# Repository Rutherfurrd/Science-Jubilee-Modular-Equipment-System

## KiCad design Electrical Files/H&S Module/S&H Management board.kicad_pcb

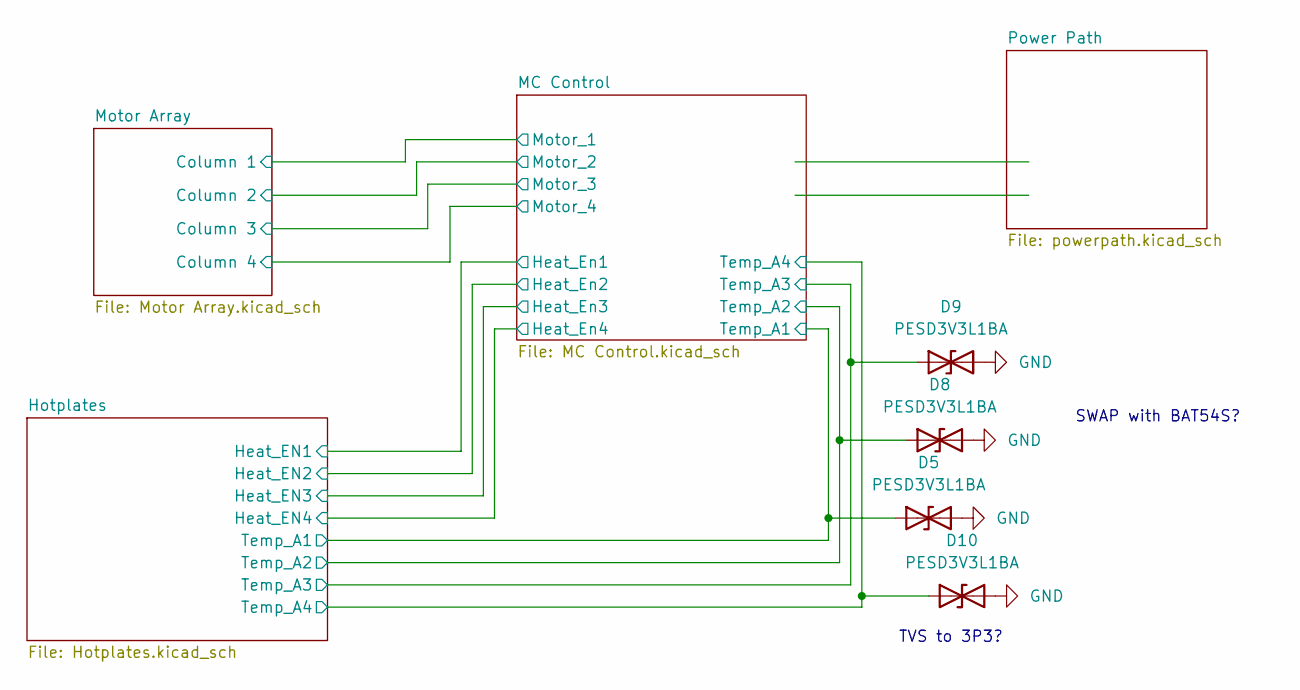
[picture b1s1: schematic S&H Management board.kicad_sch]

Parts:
D5, D8, D9, D10: PESD3V3L1BA; D_SOD-323F

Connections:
/Hotplates/Temp_A1: D5.1 (A1); also elsewhere on the board
/Hotplates/Temp_A2: D8.1 (A1); also elsewhere on the board
/Hotplates/Temp_A3: D9.1 (A1); also elsewhere on the board
/Hotplates/Temp_A4: D10.1 (A1); also elsewhere on the board
GND: D5.2 (A2), D8.2 (A2), D9.2 (A2), D10.2 (A2); also elsewhere on the board

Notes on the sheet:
SWAP with BAT54S?
TVS to 3P3?

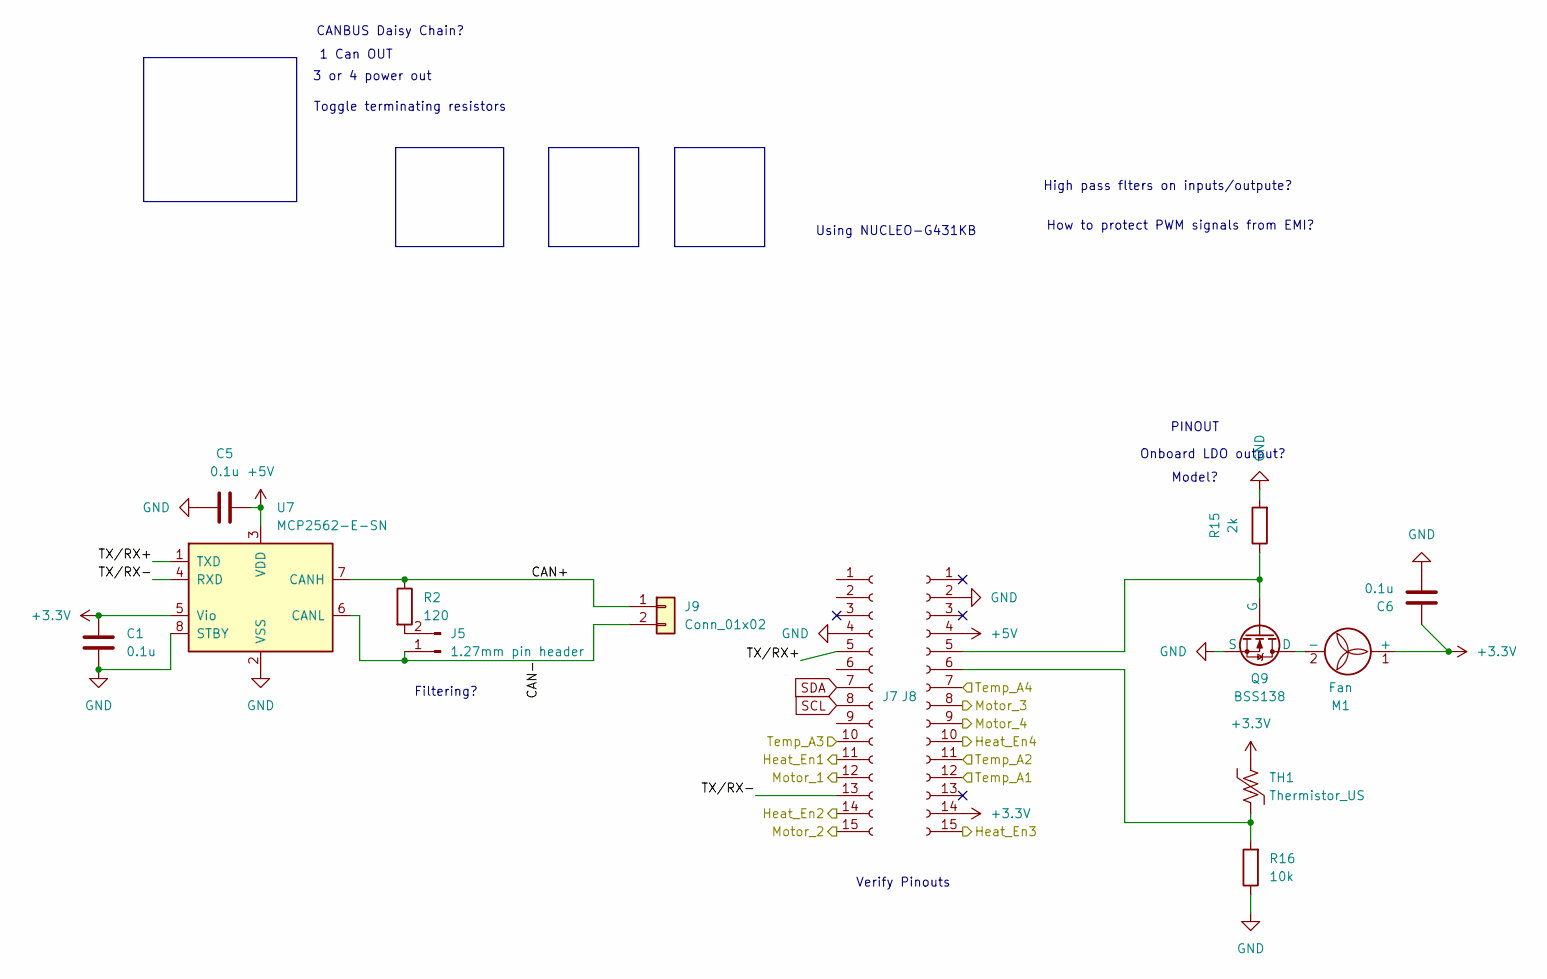
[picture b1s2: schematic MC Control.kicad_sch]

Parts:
C1, C5, C6: 0.1u; C_0603_1608Metric_Pad1.08x0.95mm_HandSolder
J5: 1.27mm pin header; PinHeader_1x02_P1.27mm_Vertical
J7, J8: PPTC151LFBN-RC; PinHeader_1x15_P2.54mm_Vertical
J9: Conn_01x02; Molex_Mini-Fit_Jr_5569-02A2_2x01_P4.20mm_Horizontal
M1: Fan; JST_PH_B2B-PH-K_1x02_P2.00mm_Vertical
Q9: BSS138; SOT-23-3
R2: 120; R_0603_1608Metric_Pad0.98x0.95mm_HandSolder
R15: 2k; R_0603_1608Metric_Pad0.98x0.95mm_HandSolder
R16: 10k; R_0603_1608Metric_Pad0.98x0.95mm_HandSolder
TH1: Thermistor_US; R_0603_1608Metric_Pad0.98x0.95mm_HandSolder
U7: MCP2562-E-SN; SOIC-8_3.9x4.9mm_P1.27mm; LCSC C124016

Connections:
+3.3V: C1.1, C6.1, J8.14, M1.1 (+), TH1.1, U7.5 (Vio); also elsewhere on the board
+5V: C5.2, J8.4, U7.3 (VDD); also elsewhere on the board
/Hotplates/Heat_EN1: J7.11; also elsewhere on the board
/Hotplates/Heat_EN2: J7.14; also elsewhere on the board
/Hotplates/Heat_EN3: J8.15; also elsewhere on the board
/Hotplates/Heat_EN4: J8.10; also elsewhere on the board
/Hotplates/Temp_A1: J8.12; also elsewhere on the board
/Hotplates/Temp_A2: J8.11; also elsewhere on the board
/Hotplates/Temp_A3: J7.10; also elsewhere on the board
/Hotplates/Temp_A4: J8.7; also elsewhere on the board
/MC Control/CAN+: J9.1, R2.1, U7.7 (CANH)
/MC Control/CAN-: J5.1, J9.2, U7.6 (CANL)
/MC Control/Motor_1: J7.12; also elsewhere on the board
/MC Control/Motor_2: J7.15; also elsewhere on the board
/MC Control/Motor_3: J8.8; also elsewhere on the board
/MC Control/Motor_4: J8.9; also elsewhere on the board
/MC Control/TX/RX+: J7.5, U7.1 (TXD)
/MC Control/TX/RX-: J7.13, U7.4 (RXD)
GND: C1.2, C5.1, C6.2, J7.4, J8.2, Q9.3 (S), R15.2, R16.1, U7.2 (VSS), U7.8 (STBY); also elsewhere on the board
unnamed: J5.2, R2.2
unnamed: J8.5, Q9.2 (G), R15.1
unnamed: J8.6, R16.2, TH1.2
unnamed: M1.2 (-), Q9.1 (D)
SCL: J7.8
SDA: J7.7

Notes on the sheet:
Using NUCLEO-G431KB
PINOUT
High pass flters on inputs/outpute?
Filtering?
3 or 4 power out
Onboard LDO output?
Verify Pinouts
CANBUS Daisy Chain?
Model?
How to protect PWM signals from EMI?
Toggle terminating resistors
1 Can OUT

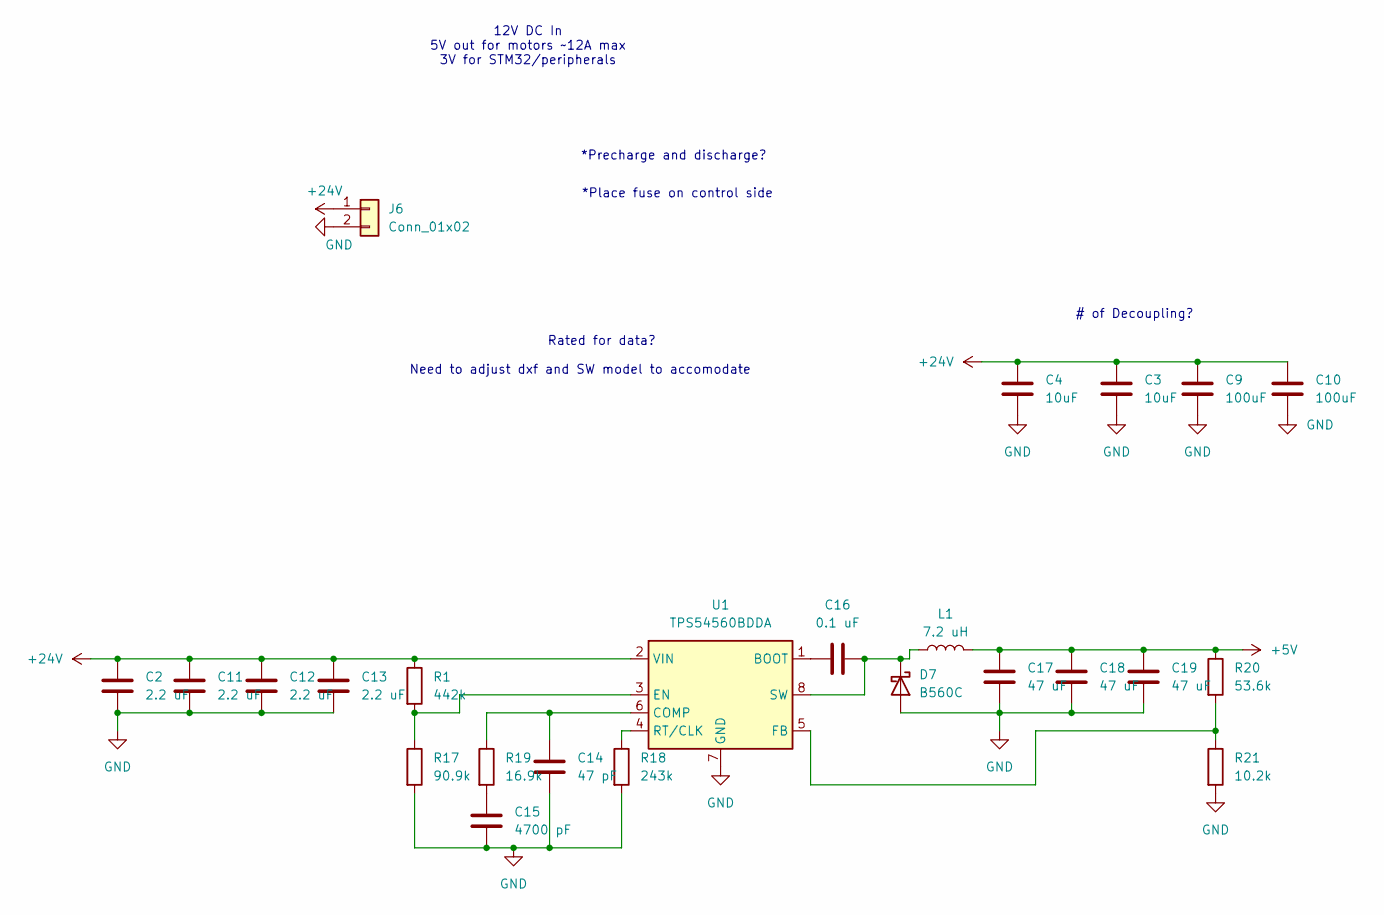
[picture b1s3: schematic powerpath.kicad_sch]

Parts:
C2, C11, C12, C13: 2.2 uF; C_0603_1608Metric_Pad1.08x0.95mm_HandSolder
C3, C4: 10uF; C_0603_1608Metric_Pad1.08x0.95mm_HandSolder
C9, C10: 100uF; C_0603_1608Metric_Pad1.08x0.95mm_HandSolder
C14: 47 pF; C_0603_1608Metric_Pad1.08x0.95mm_HandSolder
C15: 4700 pF; C_0603_1608Metric_Pad1.08x0.95mm_HandSolder
C16: 0.1 uF; C_0603_1608Metric_Pad1.08x0.95mm_HandSolder
C17, C18, C19: 47 uF; C_0603_1608Metric_Pad1.08x0.95mm_HandSolder
D7: B560C; D_SMC(DO-214AB)
J6: Conn_01x02; Molex_Mini-Fit_Jr_5569-02A2_2x01_P4.20mm_Horizontal
L1: 7.2 uH; L_Bourns_SRP7028A_7.3x6.6mm
R1: 442k; R_0603_1608Metric_Pad0.98x0.95mm_HandSolder
R17: 90.9k; R_0603_1608Metric_Pad0.98x0.95mm_HandSolder
R18: 243k; R_0603_1608Metric_Pad0.98x0.95mm_HandSolder
R19: 16.9k; R_0603_1608Metric_Pad0.98x0.95mm_HandSolder
R20: 53.6k; R_0603_1608Metric_Pad0.98x0.95mm_HandSolder
R21: 10.2k; R_0603_1608Metric_Pad0.98x0.95mm_HandSolder
U1: TPS54560BDDA; Texas_R-PDSO-G8_EP2.95x4.9mm_Mask2.4x3.1mm_ThermalVias

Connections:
+5V: C17.1, C18.1, C19.1, L1.2, R20.1; also elsewhere on the board
+24V: C2.1, C3.1, C4.1, C9.1, C10.1, C11.1, C12.1, C13.1, J6.1, R1.1, U1.2 (VIN); also elsewhere on the board
GND: C2.2, C3.2, C4.2, C9.2, C10.2, C11.2, C12.2, C13.2, C14.2, C15.2, C17.2, C18.2, C19.2, D7.2 (A), J6.2, R17.2, R18.2, R21.2, U1.7 (GND), U1.9 (GND); also elsewhere on the board
unnamed: C15.1, R19.2
unnamed: C16.2, D7.1 (K), L1.1, U1.8 (SW)
unnamed: C16.1, U1.1 (BOOT)
unnamed: C14.1, R19.1, U1.6 (COMP)
unnamed: R1.2, R17.1, U1.3 (EN)
unnamed: R20.2, R21.1, U1.5 (FB)
unnamed: R18.1, U1.4 (RT/CLK)

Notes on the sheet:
12V DC In 5V out for motors ~12A max 3V for STM32/peripherals
Need to adjust dxf and SW model to accomodate
Rated for data?
*Precharge and discharge?
# of Decoupling?
*Place fuse on control side

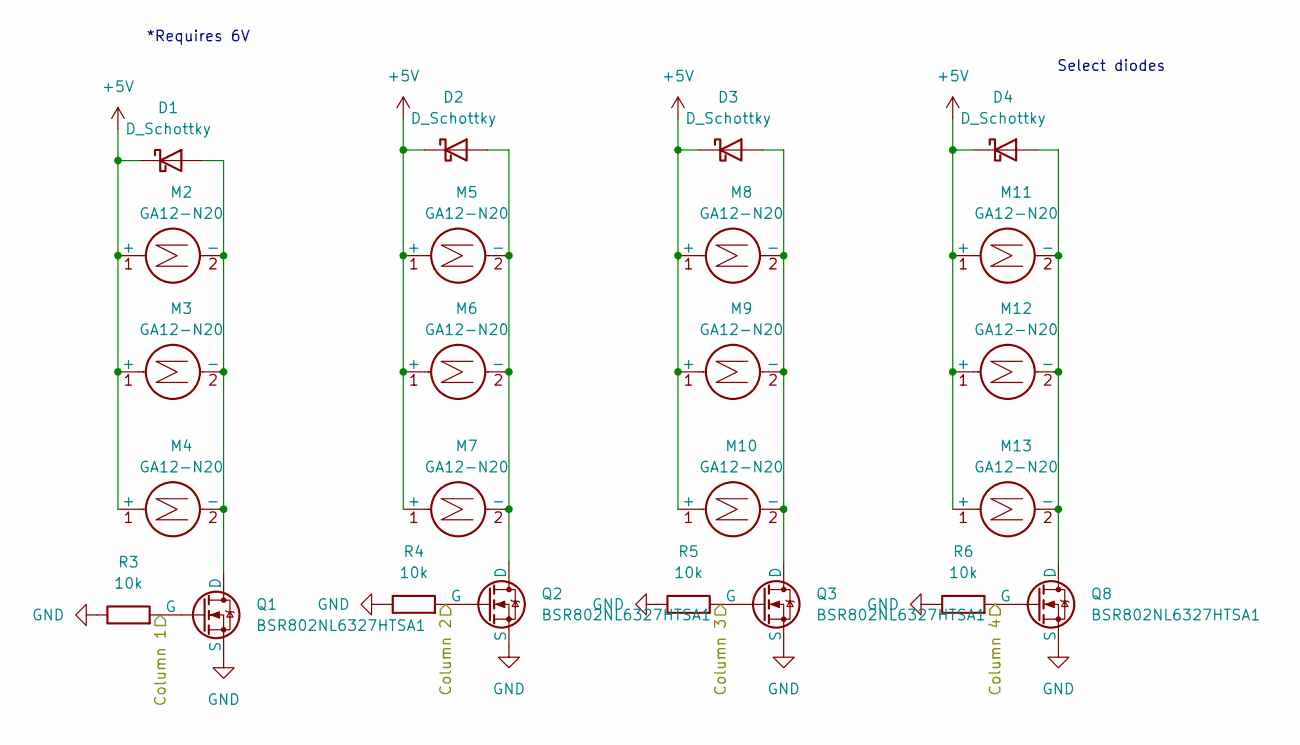
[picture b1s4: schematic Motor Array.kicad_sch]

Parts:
D1, D2, D3, D4: D_Schottky; D_SOD-323
M2, M3, M4, M5, M6, M7, M8, M9, M10, M11, M12, M13: GA12-N20
Q1, Q2, Q3, Q8: BSR802NL6327HTSA1; SC-59_Handsoldering
R3, R4, R5, R6: 10k; R_0603_1608Metric_Pad0.98x0.95mm_HandSolder

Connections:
+5V: D1.1 (K), D2.1 (K), D3.1 (K), D4.1 (K), M2.1 (+), M3.1 (+), M4.1 (+), M5.1 (+), M6.1 (+), M7.1 (+), M8.1 (+), M9.1 (+), M10.1 (+), M11.1 (+), M12.1 (+), M13.1 (+); also elsewhere on the board
/MC Control/Motor_1: Q1.2 (G), R3.2; also elsewhere on the board
/MC Control/Motor_2: Q2.2 (G), R4.2; also elsewhere on the board
/MC Control/Motor_3: Q3.2 (G), R5.2; also elsewhere on the board
/MC Control/Motor_4: Q8.2 (G), R6.2; also elsewhere on the board
GND: Q1.3 (S), Q2.3 (S), Q3.3 (S), Q8.3 (S), R3.1, R4.1, R5.1, R6.1; also elsewhere on the board
unnamed: D1.2 (A), M2.2 (-), M3.2 (-), M4.2 (-), Q1.1 (D)
unnamed: D2.2 (A), M5.2 (-), M6.2 (-), M7.2 (-), Q2.1 (D)
unnamed: D3.2 (A), M8.2 (-), M9.2 (-), M10.2 (-), Q3.1 (D)
unnamed: D4.2 (A), M11.2 (-), M12.2 (-), M13.2 (-), Q8.1 (D)

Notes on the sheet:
*Requires 6V
Select diodes

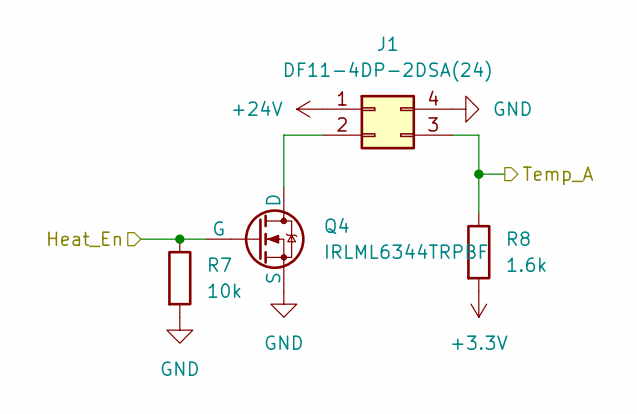
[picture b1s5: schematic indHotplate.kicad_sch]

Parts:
J1: DF11-4DP-2DSA(24); Hirose_DF11-4DP-2DSA_2x02_P2.00mm_Vertical
Q4: IRLML6344TRPBF; SC-59_Handsoldering
R7: 10k; R_0603_1608Metric_Pad0.98x0.95mm_HandSolder
R8: 1.6k; R_0603_1608Metric_Pad0.98x0.95mm_HandSolder

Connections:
+3.3V: R8.2; also elsewhere on the board
+24V: J1.1; also elsewhere on the board
/Hotplates/Heat_EN1: Q4.2 (G), R7.1; also elsewhere on the board
/Hotplates/Temp_A1: J1.3, R8.1; also elsewhere on the board
GND: J1.4, Q4.3 (S), R7.2; also elsewhere on the board
unnamed: J1.2, Q4.1 (D)

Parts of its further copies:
J2, J3, J4: DF11-4DP-2DSA(24); Hirose_DF11-4DP-2DSA_2x02_P2.00mm_Vertical
Q5, Q6, Q7: IRLML6344TRPBF; SC-59_Handsoldering
R9, R11, R13: 10k; R_0603_1608Metric_Pad0.98x0.95mm_HandSolder
R10, R12, R14: 1.6k; R_0603_1608Metric_Pad0.98x0.95mm_HandSolder

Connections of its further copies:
+3.3V: R10.2, R12.2, R14.2; also elsewhere on the board
+24V: J2.1, J3.1, J4.1; also elsewhere on the board
/Hotplates/Heat_EN2: Q5.2 (G), R9.1; also elsewhere on the board
/Hotplates/Heat_EN3: Q6.2 (G), R11.1; also elsewhere on the board
/Hotplates/Heat_EN4: Q7.2 (G), R13.1; also elsewhere on the board
/Hotplates/Temp_A2: J2.3, R10.1; also elsewhere on the board
/Hotplates/Temp_A3: J3.3, R12.1; also elsewhere on the board
/Hotplates/Temp_A4: J4.3, R14.1; also elsewhere on the board
GND: J2.4, J3.4, J4.4, Q5.3 (S), Q6.3 (S), Q7.3 (S), R9.2, R11.2, R13.2; also elsewhere on the board
unnamed: J2.2, Q5.1 (D)
unnamed: J3.2, Q6.1 (D)
unnamed: J4.2, Q7.1 (D)

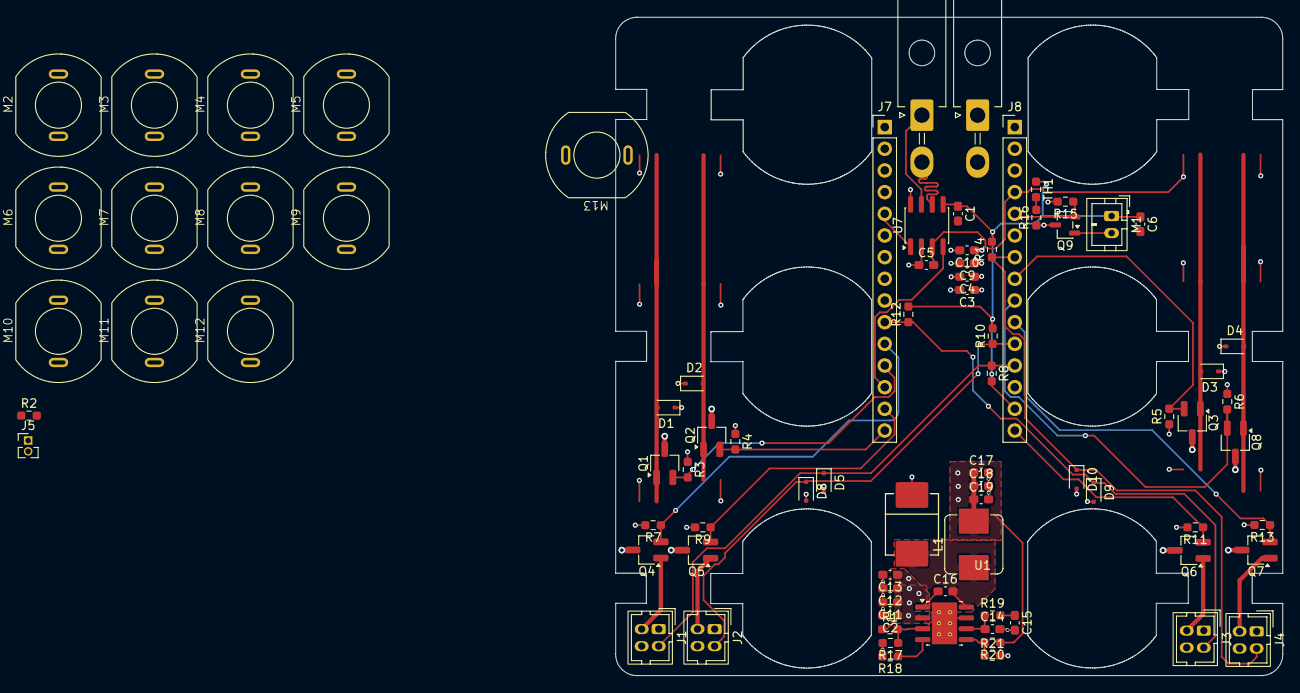
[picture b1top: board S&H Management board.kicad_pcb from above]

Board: 4 copper layers, 78.2 x 77.2 mm, 82 parts (0 on the bottom side), 39 nets.

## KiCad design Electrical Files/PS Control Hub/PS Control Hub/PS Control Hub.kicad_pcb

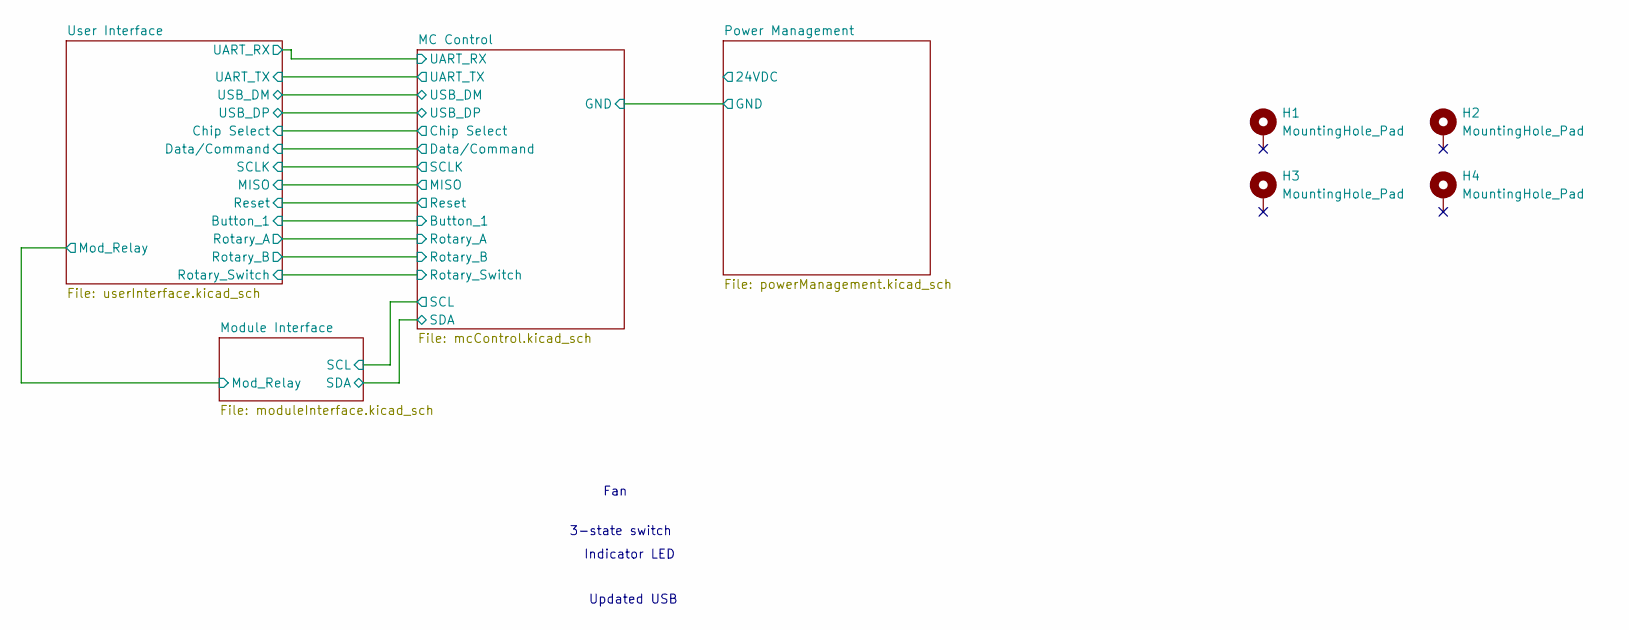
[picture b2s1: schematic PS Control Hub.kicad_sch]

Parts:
H1, H2, H3, H4: MountingHole_Pad; MountingHole_3.2mm_M3_DIN965_Pad_TopBottom

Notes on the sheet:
Updated USB
Fan
Indicator LED
3-state switch

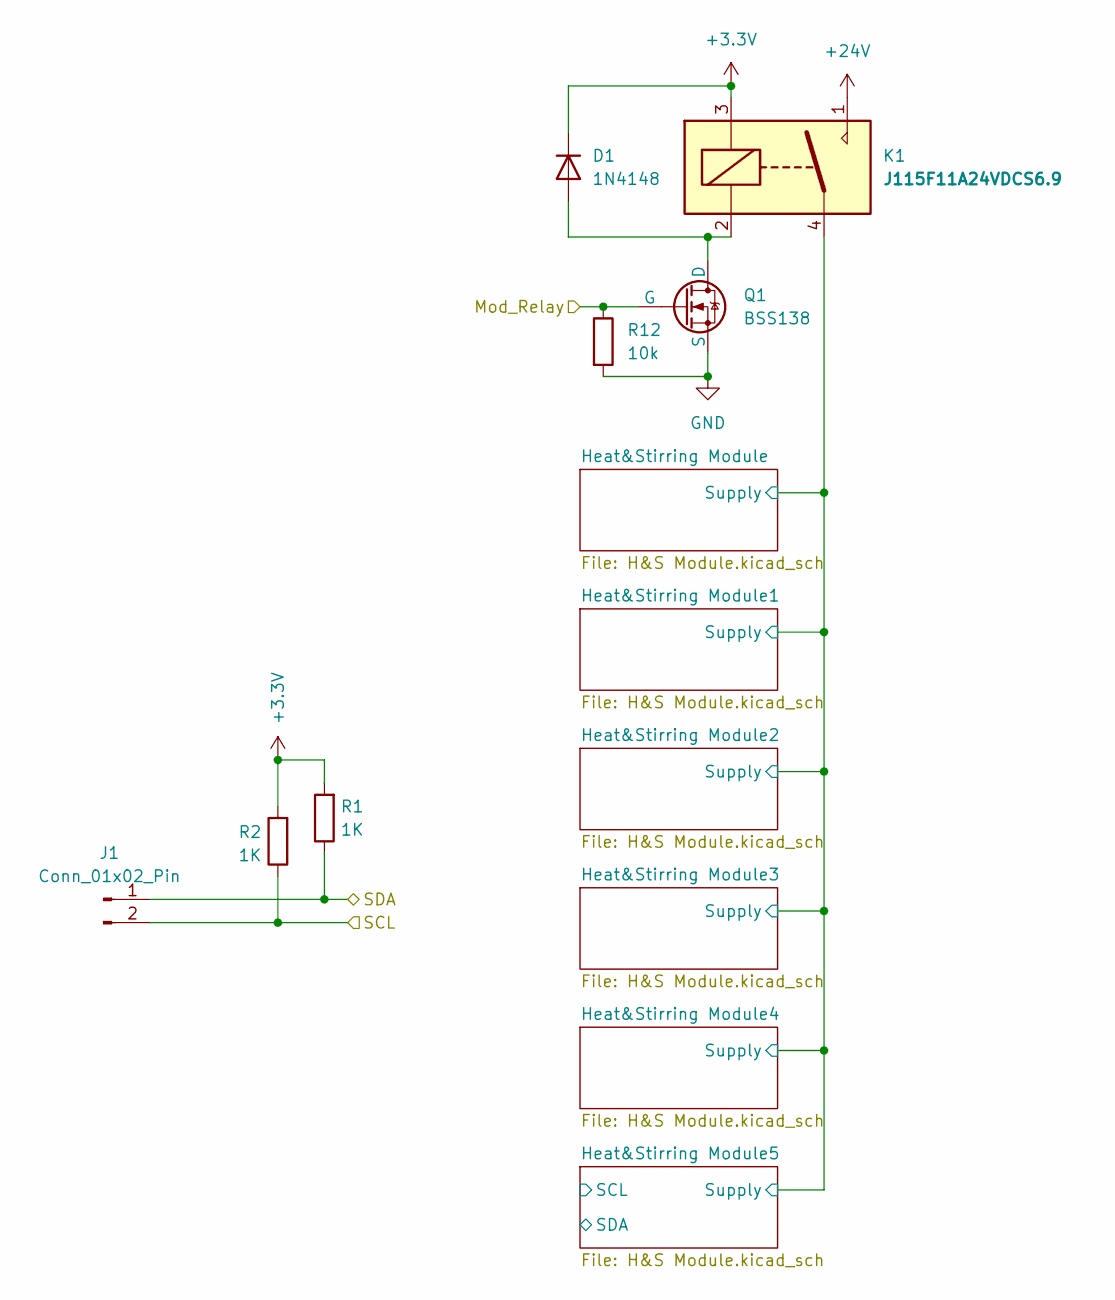
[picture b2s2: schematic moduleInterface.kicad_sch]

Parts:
D1: 1N4148; D_DO-35_SOD27_P7.62mm_Horizontal
J1: Conn_01x02_Pin; Molex_Mini-Fit_Jr_5566-02A_2x01_P4.20mm_Vertical
K1: J115F11A24VDCS6.9; J115F1_1A_S_6_CRS
Q1: BSS138; SOT-23-3
R1, R2: 1K; R_0805_2012Metric_Pad1.20x1.40mm_HandSolder
R12: 10k; R_0805_2012Metric_Pad1.20x1.40mm_HandSolder

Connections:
+3.3V: D1.1 (K), K1.3, R1.2, R2.2; also elsewhere on the board
+24V: K1.1; also elsewhere on the board
/MC Control/SCL: J1.2, R2.1; also elsewhere on the board
/MC Control/SDA: J1.1, R1.1; also elsewhere on the board
/Module Interface/Heat&Stirring Module/Supply: K1.4; also elsewhere on the board
/Module Interface/Mod_Relay: Q1.2 (G), R12.1; also elsewhere on the board
GND: Q1.3 (S), R12.2; also elsewhere on the board
unnamed: D1.2 (A), K1.2, Q1.1 (D)

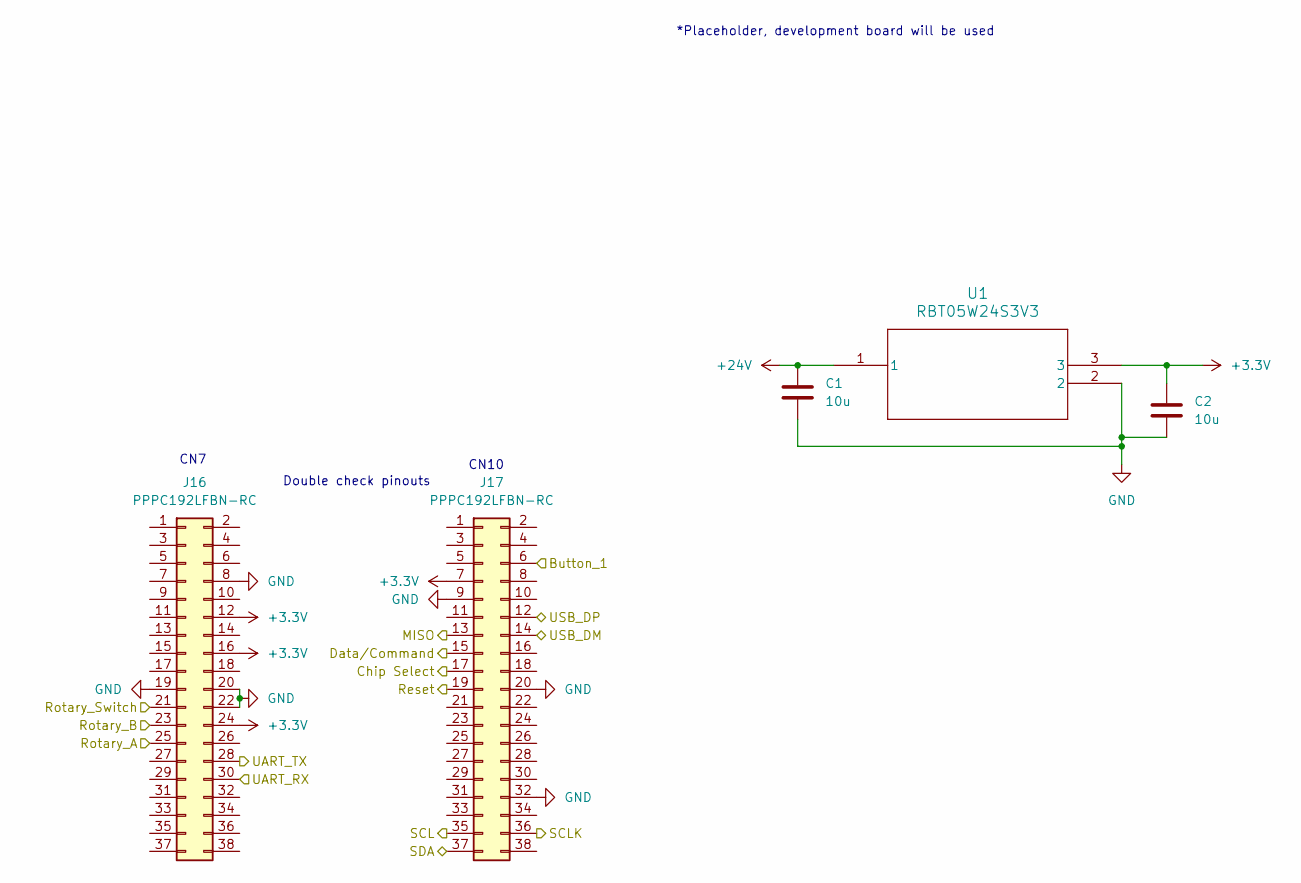
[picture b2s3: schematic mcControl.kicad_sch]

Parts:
C1, C2: 10u; C_0805_2012Metric_Pad1.18x1.45mm_HandSolder
J16, J17: PPPC192LFBN-RC; PinSocket_2x19_P2.54mm_Vertical
U1: RBT05W24S3V3; RBT10W24S05_XPP_XPR

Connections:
+3.3V: C2.1, J16.12, J16.16, J16.24, J17.7, U1.3; also elsewhere on the board
+24V: C1.1, U1.1; also elsewhere on the board
/MC Control/Button_1: J17.6; also elsewhere on the board
/MC Control/Chip Select: J17.17; also elsewhere on the board
/MC Control/Data/Command: J17.15; also elsewhere on the board
/MC Control/MISO: J17.13; also elsewhere on the board
/MC Control/Reset: J17.19; also elsewhere on the board
/MC Control/Rotary_A: J16.25; also elsewhere on the board
/MC Control/Rotary_B: J16.23; also elsewhere on the board
/MC Control/Rotary_Switch: J16.21; also elsewhere on the board
/MC Control/SCL: J17.35; also elsewhere on the board
/MC Control/SCLK: J17.36; also elsewhere on the board
/MC Control/SDA: J17.37; also elsewhere on the board
/MC Control/UART_RX: J16.30; also elsewhere on the board
/MC Control/UART_TX: J16.28; also elsewhere on the board
/MC Control/USB_DM: J17.14
/MC Control/USB_DP: J17.12
GND: C1.2, C2.2, J16.8, J16.19, J16.20, J16.22, J17.9, J17.20, J17.32, U1.2; also elsewhere on the board

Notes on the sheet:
Double check pinouts
*Placeholder, development board will be used
CN10
CN7

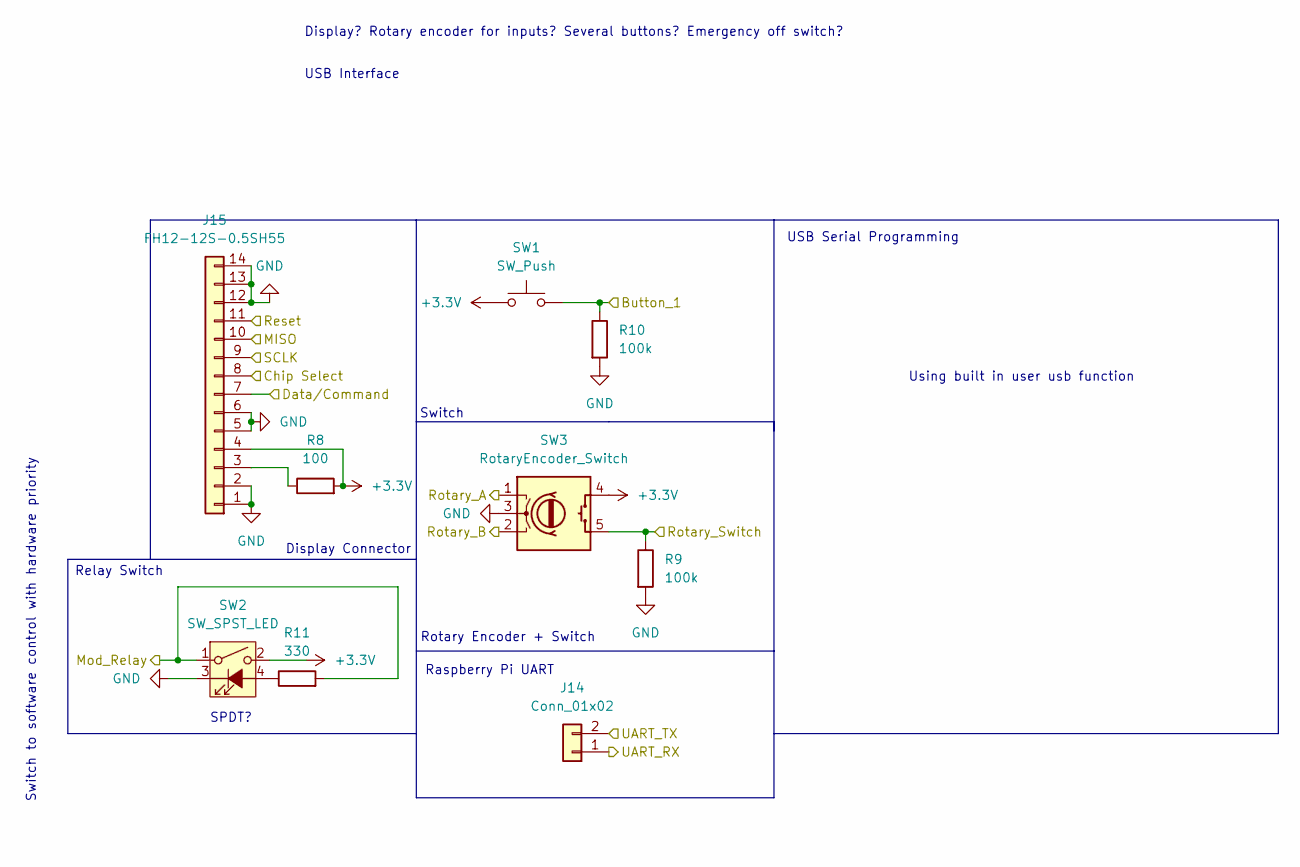
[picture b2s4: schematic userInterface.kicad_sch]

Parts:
J14: Conn_01x02; Molex_Mini-Fit_Jr_5566-02A_2x01_P4.20mm_Vertical
J15: FH12-12S-0.5SH55
R8: 100; R_0805_2012Metric_Pad1.20x1.40mm_HandSolder
R9, R10: 100k; R_0805_2012Metric_Pad1.20x1.40mm_HandSolder
R11: 330; R_0805_2012Metric_Pad1.20x1.40mm_HandSolder
SW1: SW_Push; JST_PH_B2B-PH-K_1x02_P2.00mm_Vertical
SW2: SW_SPST_LED; JST_PH_B4B-PH-K_1x04_P2.00mm_Vertical
SW3: RotaryEncoder_Switch; JST_PH_B5B-PH-K_1x05_P2.00mm_Vertical

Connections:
+3.3V: J15.4, R8.2, SW1.1, SW2.2, SW3.4 (S1); also elsewhere on the board
/MC Control/Button_1: R10.1, SW1.2; also elsewhere on the board
/MC Control/Chip Select: J15.8; also elsewhere on the board
/MC Control/Data/Command: J15.7; also elsewhere on the board
/MC Control/MISO: J15.10; also elsewhere on the board
/MC Control/Reset: J15.11; also elsewhere on the board
/MC Control/Rotary_A: SW3.1 (A); also elsewhere on the board
/MC Control/Rotary_B: SW3.2 (B); also elsewhere on the board
/MC Control/Rotary_Switch: R9.1, SW3.5 (S2); also elsewhere on the board
/MC Control/SCLK: J15.9; also elsewhere on the board
/MC Control/UART_RX: J14.1; also elsewhere on the board
/MC Control/UART_TX: J14.2; also elsewhere on the board
/Module Interface/Mod_Relay: R11.2, SW2.1; also elsewhere on the board
GND: J15.1, J15.2, J15.5, J15.6, J15.12, J15.13, J15.14, R9.2, R10.2, SW2.3 (K), SW3.3 (C); also elsewhere on the board
unnamed: J15.3, R8.1
unnamed: R11.1, SW2.4 (A)

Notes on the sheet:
Switch
USB Serial Programming
Display? Rotary encoder for inputs? Several buttons? Emergency off switch?
Relay Switch
Raspberry Pi UART
USB Interface
Display Connector
Rotary Encoder + Switch
Switch to software control with hardware priority
Using built in user usb function
SPDT?

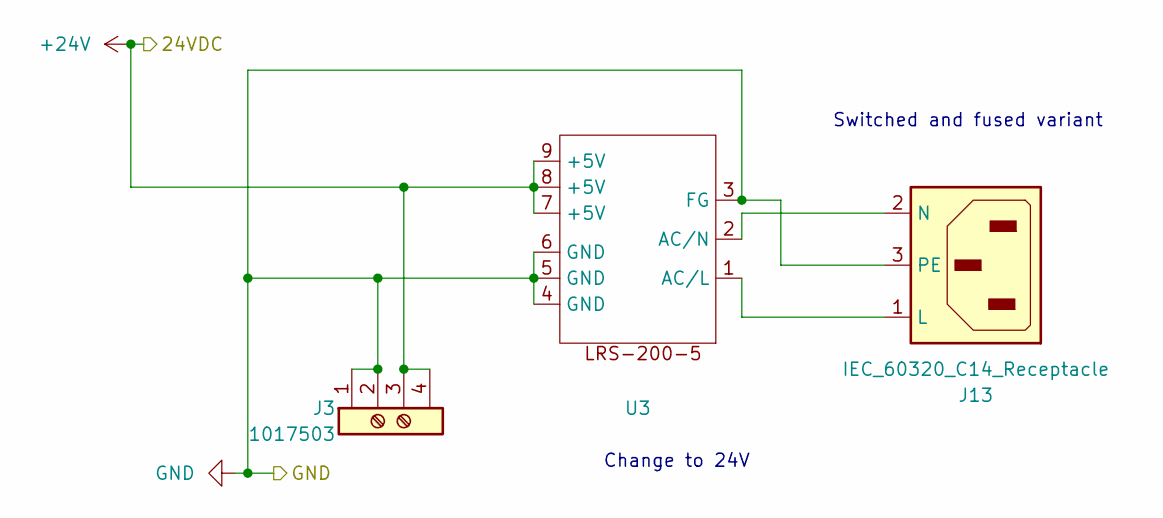
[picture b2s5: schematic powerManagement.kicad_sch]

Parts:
J3: 1017503; CONN_1017491
J13: IEC_60320_C14_Receptacle
U3: (no value)

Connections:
+24V: J3.3 (Pin_2), J3.4 (Pin_2), U3.7 (+5V), U3.8 (+5V), U3.9 (+5V); also elsewhere on the board
GND: J3.1, J3.2 (Pin_1), J13.3 (PE), U3.3 (FG), U3.4 (GND), U3.5 (GND), U3.6 (GND); also elsewhere on the board
unnamed: J13.1 (L), U3.1 (AC/L)
unnamed: J13.2 (N), U3.2 (AC/N)

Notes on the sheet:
Switched and fused variant
Change to 24V

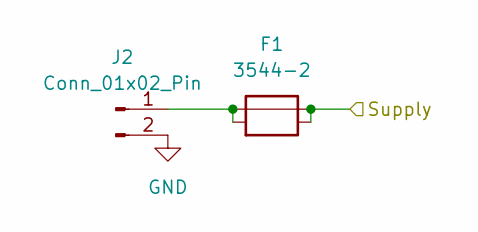
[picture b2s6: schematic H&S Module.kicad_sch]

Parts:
F1: 3544-2; CONN_3544-2_KEY
J2: Conn_01x02_Pin; Molex_Mini-Fit_Jr_5566-02A_2x01_P4.20mm_Vertical

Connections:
/Module Interface/Heat&Stirring Module/Supply: F1.3, F1.4; also elsewhere on the board
GND: J2.2; also elsewhere on the board
unnamed: F1.1, F1.2, J2.1

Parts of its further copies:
F2, F3, F4, F5, F6: 3544-2; CONN_3544-2_KEY
J4, J6, J8, J10, J12: Conn_01x02_Pin; Molex_Mini-Fit_Jr_5566-02A_2x01_P4.20mm_Vertical

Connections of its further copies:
/Module Interface/Heat&Stirring Module/Supply: F2.3, F2.4, F3.3, F3.4, F4.3, F4.4, F5.3, F5.4, F6.3, F6.4; also elsewhere on the board
GND: J4.2, J6.2, J8.2, J10.2, J12.2; also elsewhere on the board
unnamed: F2.1, F2.2, J4.1
unnamed: F3.1, F3.2, J6.1
unnamed: F4.1, F4.2, J8.1
unnamed: F5.1, F5.2, J10.1
unnamed: F6.1, F6.2, J12.1

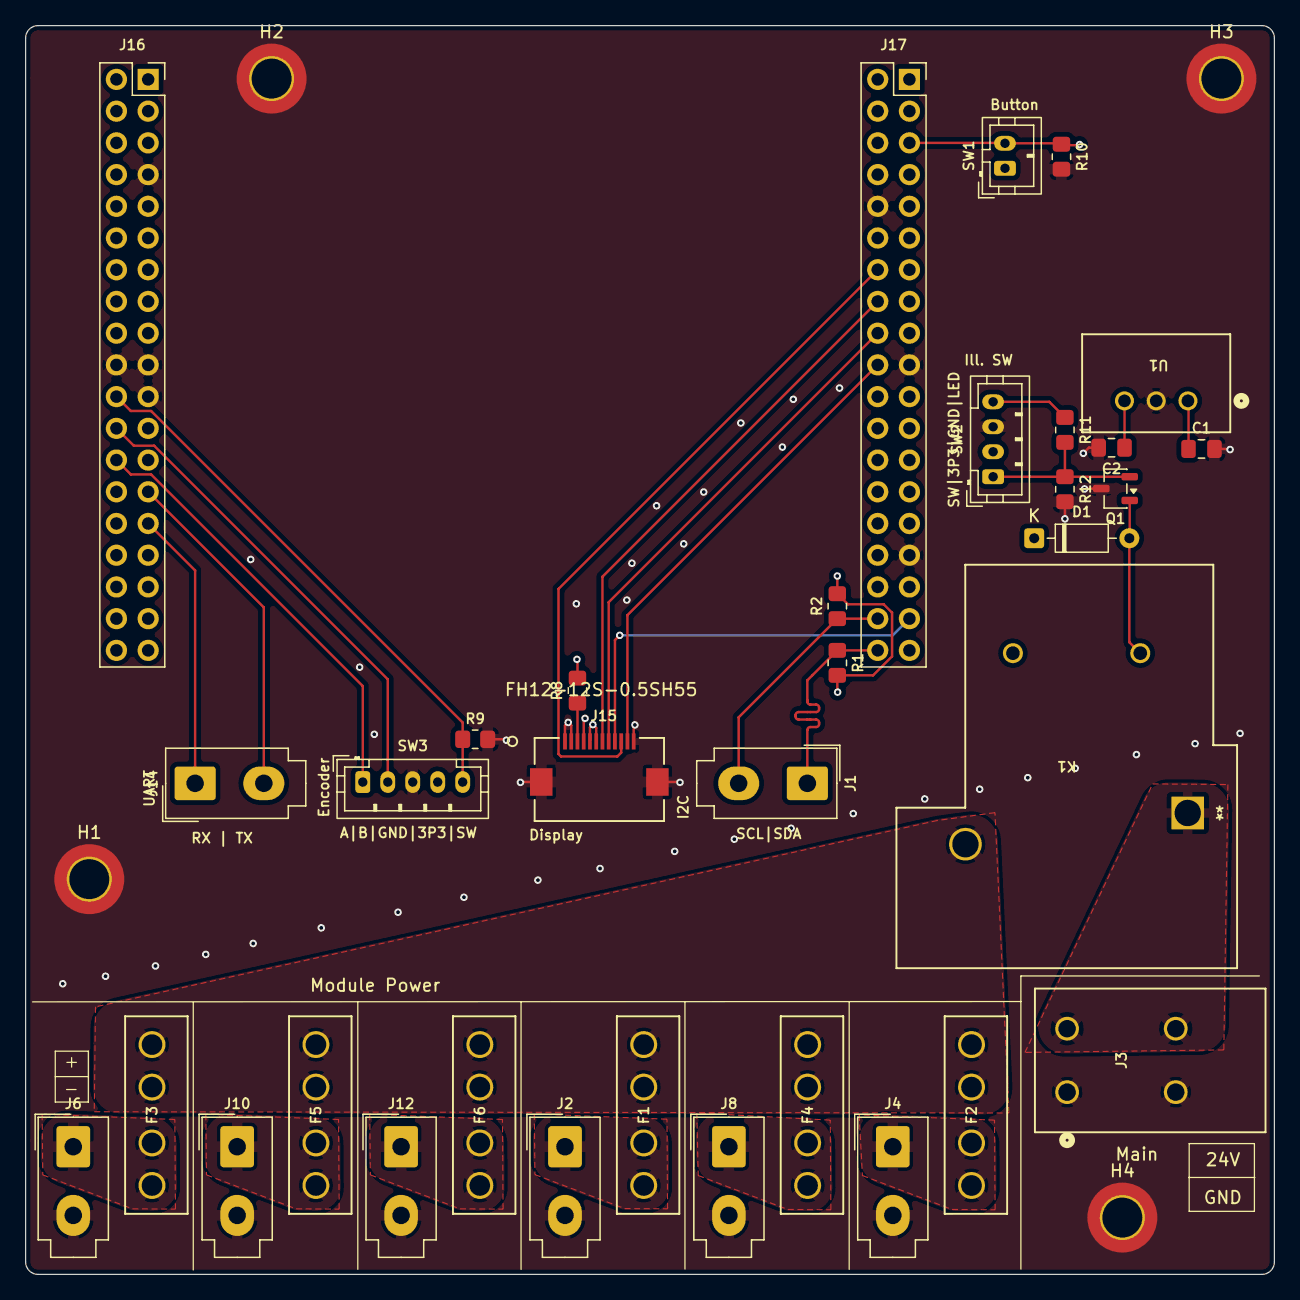
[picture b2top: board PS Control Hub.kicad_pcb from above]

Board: 4 copper layers, 100.0 x 100.0 mm, 38 parts (0 on the bottom side), 27 nets.

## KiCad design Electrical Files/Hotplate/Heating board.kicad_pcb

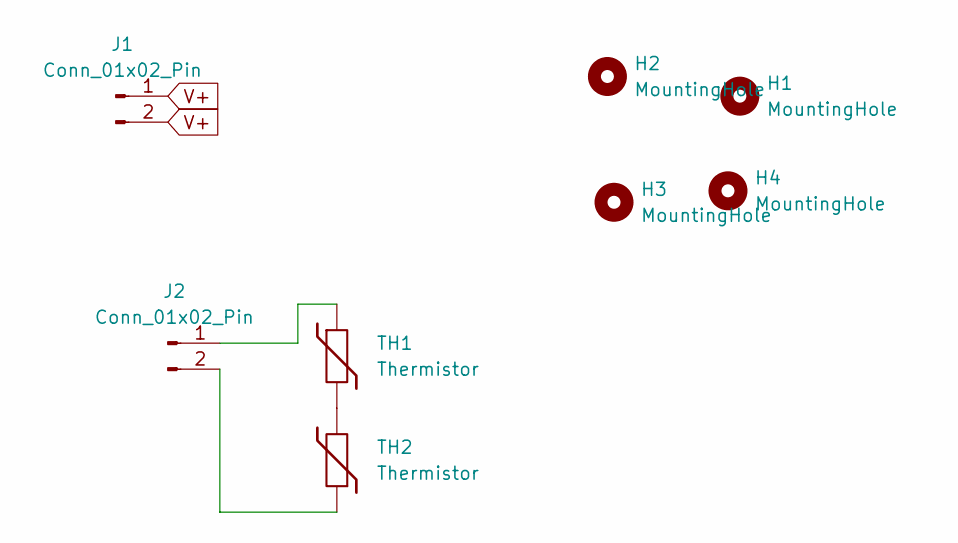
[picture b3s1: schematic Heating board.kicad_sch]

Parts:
H1, H2, H3, H4: MountingHole; MountingHole_2.2mm_M2_DIN965_Pad_TopBottom
J1, J2: Conn_01x02_Pin; SolderWire-0.1sqmm_1x02_P3.6mm_D0.4mm_OD1mm
TH1: Thermistor; C_0603_1608Metric_Pad1.08x0.95mm_HandSolder
TH2: Thermistor; R_0603_1608Metric_Pad0.98x0.95mm_HandSolder

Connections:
unnamed: J2.1, TH1.1
unnamed: J2.2, TH2.1
unnamed: TH1.2, TH2.2
V+: J1.1, J1.2

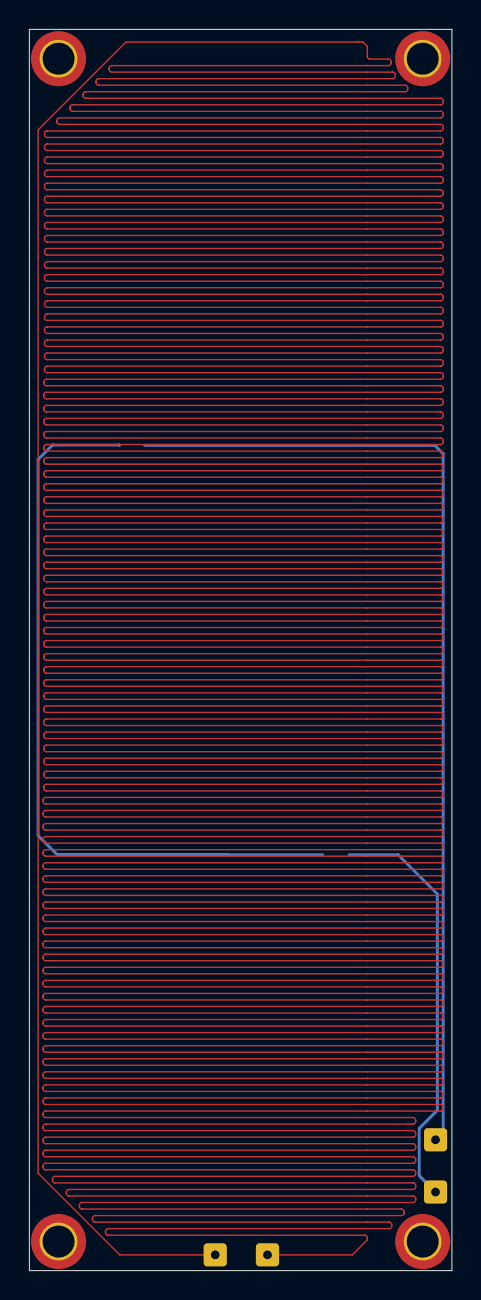
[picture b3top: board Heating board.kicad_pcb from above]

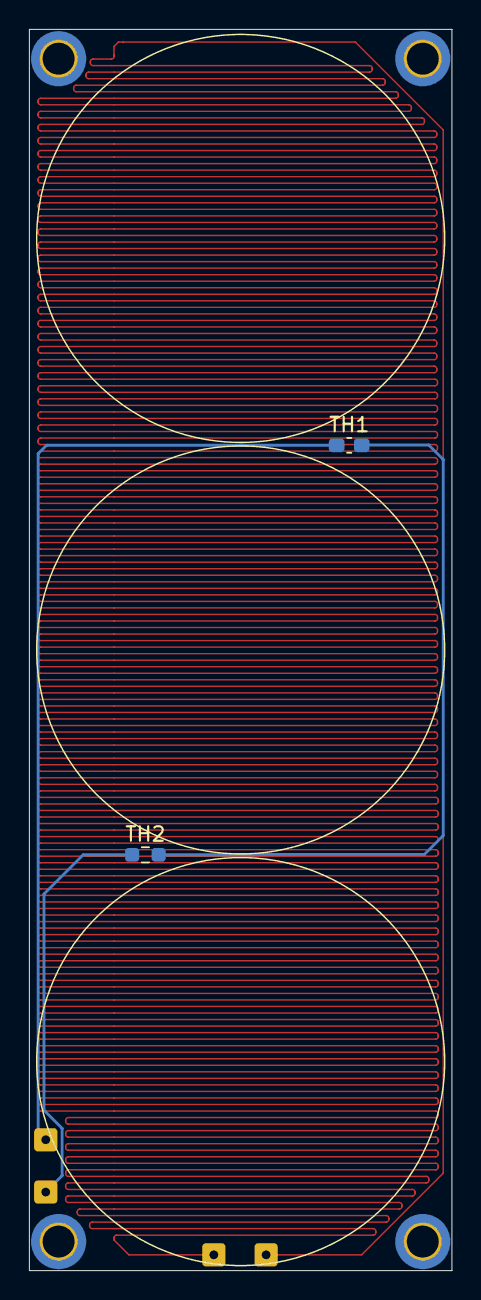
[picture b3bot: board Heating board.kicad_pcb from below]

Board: 2 copper layers, 29.1 x 85.5 mm, 8 parts (2 on the bottom side), 4 nets.

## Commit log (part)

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2026-03-13 Control Hub Housing
2026-04-16 Control Hub Housing, H&S PCB
2026-05-28 Control Hub, Flexible Hotplate, Housing Fan

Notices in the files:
parts and their libraries:
Copyright 2016 Accelerated Designs. All rights reserved.
